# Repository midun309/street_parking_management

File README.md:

View this project on [CADLAB.io](https://cadlab.io/project/29315). 

# street_parking_management

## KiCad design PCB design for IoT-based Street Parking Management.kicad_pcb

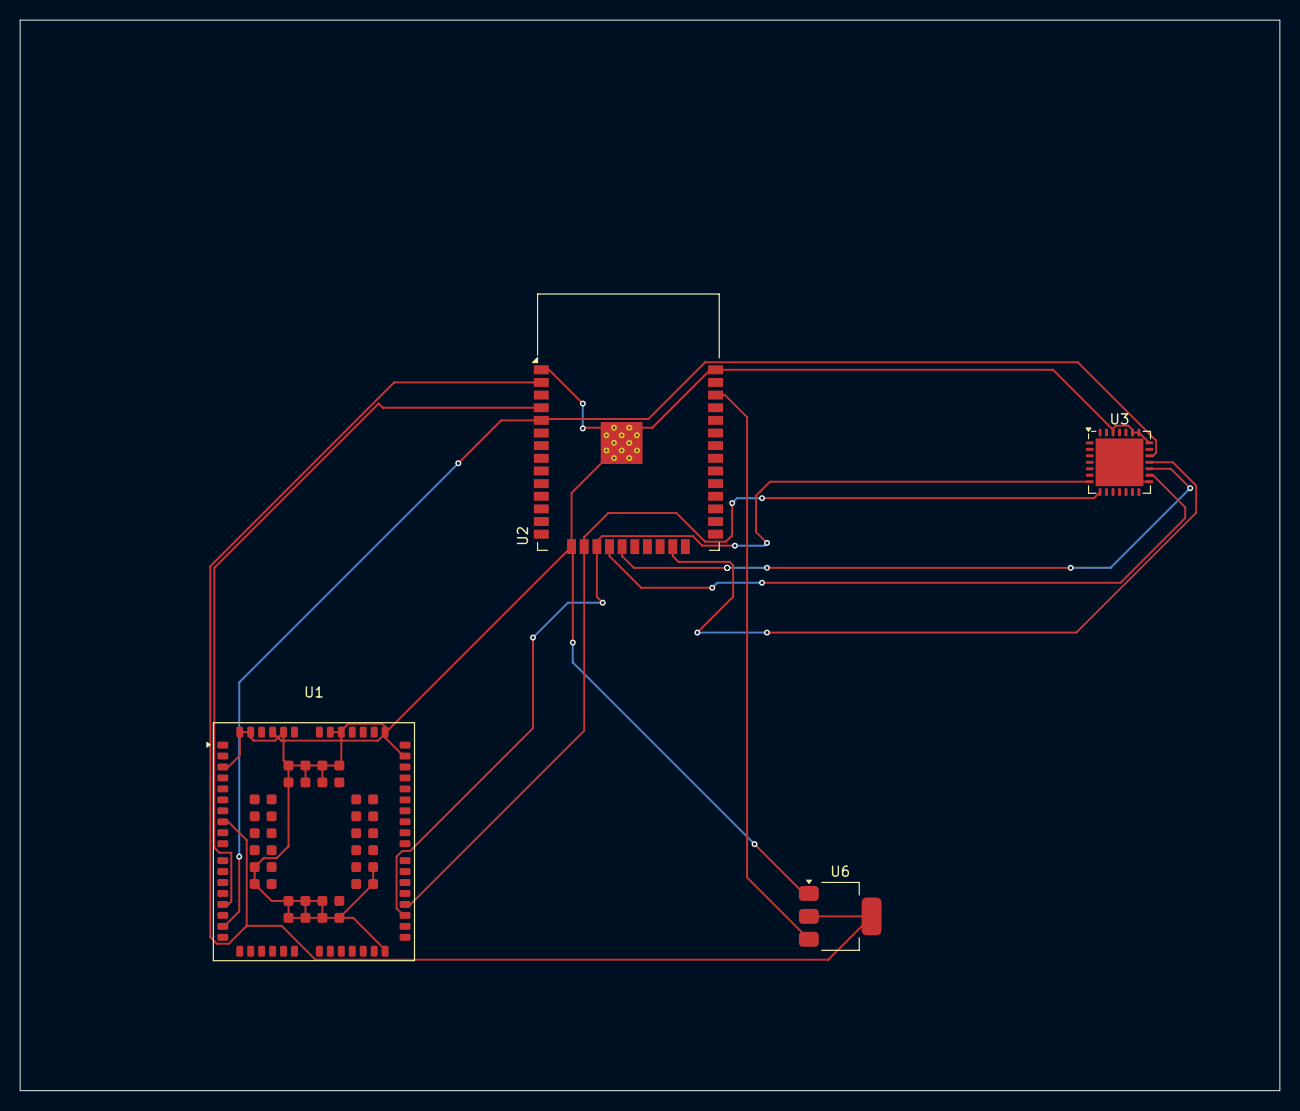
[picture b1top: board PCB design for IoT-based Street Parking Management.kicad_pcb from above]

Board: 2 copper layers, 126.5 x 107.5 mm, 4 parts (0 on the bottom side), 10 nets.

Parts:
U1: BG95-M1; Quectel_BG95
U2: ESP32-WROOM-32
U3: SX1278; QFN-28-1EP_6x6mm_P0.65mm_EP4.8x4.8mm
U6: AMS1117; SOT-223-3_TabPin2

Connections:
+12V: U1.8 (VBUS), U2.2 (VDD), U6.2 (VO)
/dio0: U1.35 (MAIN_TXD), U2.16 (IO13), U3.8 (DIO0)
/miso: U2.19 (SCS/CMD), U3.17 (MISO)
/mosi: U2.23 (IO15), U3.18 (MOSI)
/nss: U1.17 (~RESET), U2.5 (SENSOR_VN), U3.19 (NSS)
/pwrket: U1.15 (PWRKEY), U2.4 (SENSOR_VP)
/reset: U1.34 (MAIN_RXD), U2.17 (SHD/SD2), U3.7 (~RESET)
/sck: U2.18 (SWP/SD3), U3.16 (SCK)
/vin: U2.36 (IO22), U6.3 (VI)
GND: U1.3 (GND), U1.31 (GND), U1.48 (GND), U1.50 (GND), U1.54 (GND), U1.55 (GND), U1.58 (GND), U1.59 (GND), U1.61 (GND), U1.62 (GND), U1.67 (GND), U1.68 (GND), U1.69 (GND), U1.70 (GND), U1.71 (GND), U1.72 (GND), U1.73 (GND), U1.74 (GND), U1.79 (GND), U1.80 (GND), U1.81 (GND), U1.82 (GND), U1.89 (GND), U1.90 (GND), U1.91 (GND), U1.100 (GND), U1.101 (GND), U1.102 (GND), U2.1 (GND), U2.15 (GND), U2.38 (GND), U2.39 (GND), U3.15 (GND), U3.21 (GND), U3.22 (GND), U3.23 (GND), U3.26 (GND), U3.29 (GND), U6.1 (ADJ)

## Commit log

2025-04-29 pcb assignment
2025-04-29 Backlink to CADLAB.io has been added.
